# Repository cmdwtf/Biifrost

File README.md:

# Biifröst Bridge
A PCB bridge from Odiin to Screen

### Board Images

# EDA
Biifröst Bridge was designed and created with [KiCad EDA](https://kicad.org/) 5.1.6.

# License
This repository is licensed under Apache-2.0 WITH SHL-2.1. Please see LICENSE.md for more information.

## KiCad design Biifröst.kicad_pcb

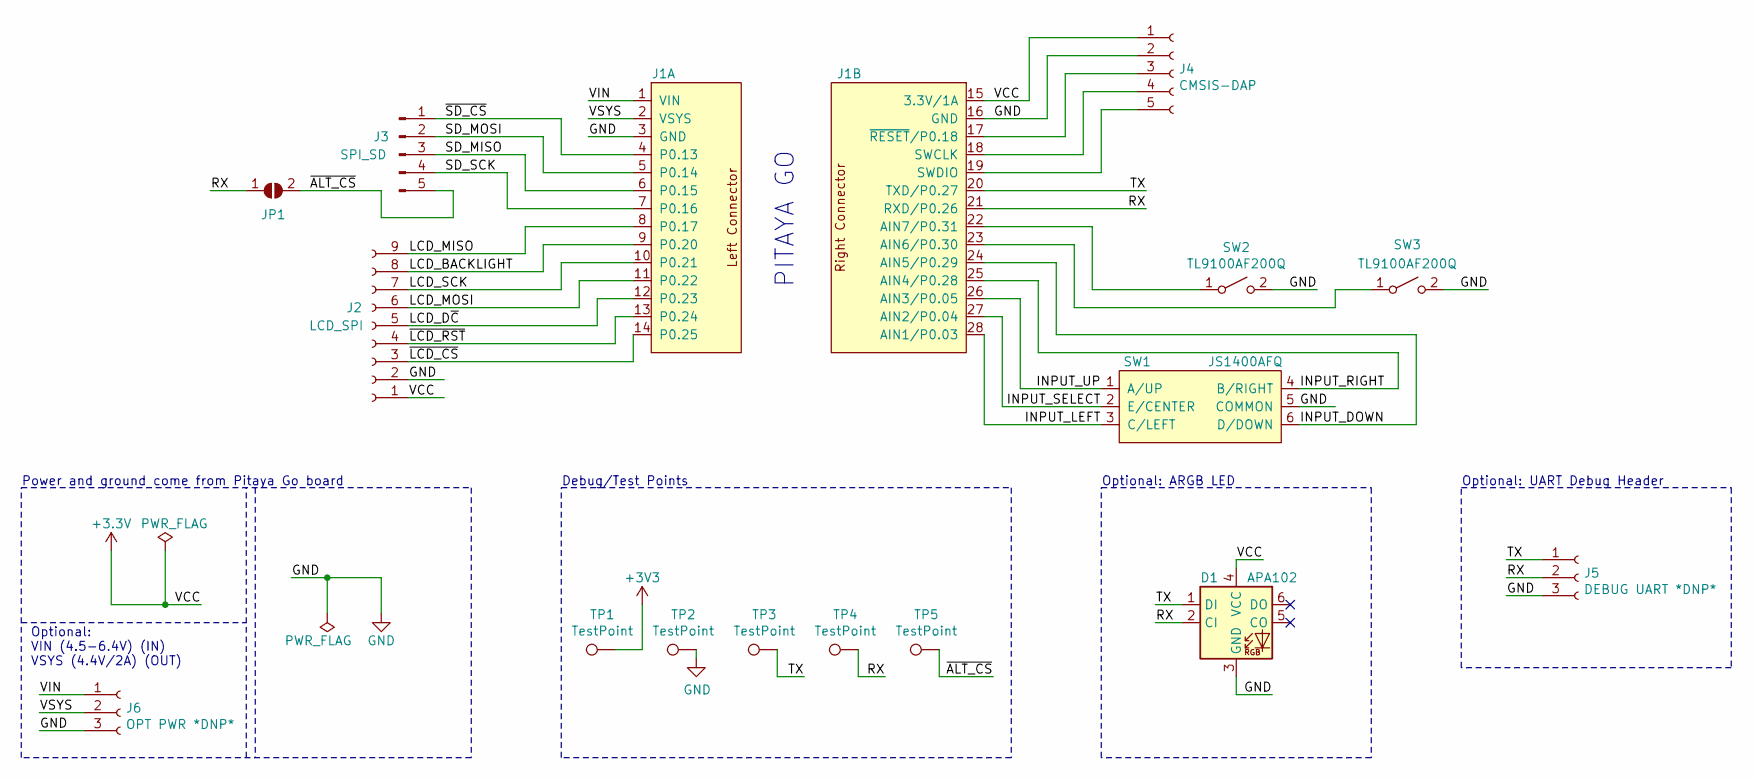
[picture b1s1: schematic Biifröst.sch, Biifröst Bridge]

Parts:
D1: APA102; LED_RGB_5050-6
J1: Pitaya_Go; Pitaya_Go_Headers
J2: LCD_SPI; PinHeader_1x09_P2.54mm_Vertical
J3: SPI_SD; PinHeader_1x05_P2.54mm_Vertical
J4: CMSIS-DAP; PinHeader_1x05_P2.54mm_Horizontal
J5: DEBUG UART *DNP*; PinHeader_1x03_P2.54mm_Horizontal
J6: OPT PWR *DNP*; PinHeader_1x03_P2.54mm_Horizontal
JP1: SolderJumper_2_Open; SolderJumper-2_P1.3mm_Open_TrianglePad1.0x1.5mm
SW1: JS1400AFQ; JS1400
SW2, SW3: TL9100AF200Q; TL9100
TP1, TP2, TP3, TP4, TP5: TestPoint; TestPoint_Pad_D1.5mm

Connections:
/INPUT_DOWN: J1.24 (AIN5/P0.29), SW1.6 (D/DOWN)
/INPUT_LEFT: J1.28 (AIN1/P0.03), SW1.3 (C/LEFT)
/INPUT_RIGHT: J1.25 (AIN4/P0.28), SW1.4 (B/RIGHT)
/INPUT_SELECT: J1.27 (AIN2/P0.04), SW1.2 (E/CENTER)
/INPUT_UP: J1.26 (AIN3/P0.05), SW1.1 (A/UP)
/LCD_BACKLIGHT: J1.9 (P0.20), J2.8
/LCD_D~C~: J1.12 (P0.23), J2.5
/LCD_MISO: J1.8 (P0.17), J2.9
/LCD_MOSI: J1.11 (P0.22), J2.6
/LCD_SCK: J1.10 (P0.21), J2.7
/RX: D1.2 (CI), J1.21 (RXD/P0.26), J5.2, JP1.1 (A), TP4.1
/SD_MISO: J1.6 (P0.15), J3.3
/SD_MOSI: J1.5 (P0.14), J3.2
/SD_SCK: J1.7 (P0.16), J3.4
/TX: D1.1 (DI), J1.20 (TXD/P0.27), J5.1, TP3.1
/VIN: J1.1 (VIN), J6.1
/VSYS: J1.2 (VSYS), J6.2
/~ALT_CS~: J3.5, JP1.2 (B), TP5.1
/~LCD_CS~: J1.14 (P0.25), J2.3
/~LCD_RST~: J1.13 (P0.24), J2.4
/~SD_CS~: J1.4 (P0.13), J3.1
GND: D1.3 (GND), J1.3 (GND), J1.16 (GND), J2.2, J4.2, J5.3, J6.3, SW1.5 (COMMON), SW2.2 (B), SW3.2 (B), TP2.1
unnamed: J1.17 (~RESET~/P0.18), J4.3
unnamed: J1.18 (SWCLK), J4.4
unnamed: J1.19 (SWDIO), J4.5
unnamed: J1.22 (AIN7/P0.31), SW2.1 (A)
unnamed: J1.23 (AIN6/P0.30), SW3.1 (A)

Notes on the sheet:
PITAYA GO
Power and ground come from Pitaya Go board
Optional: ARGB LED
Optional: UART Debug Header
Debug/Test Points
Optional: VIN (4.5-6.4V) (IN) VSYS (4.4V/2A) (OUT)

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
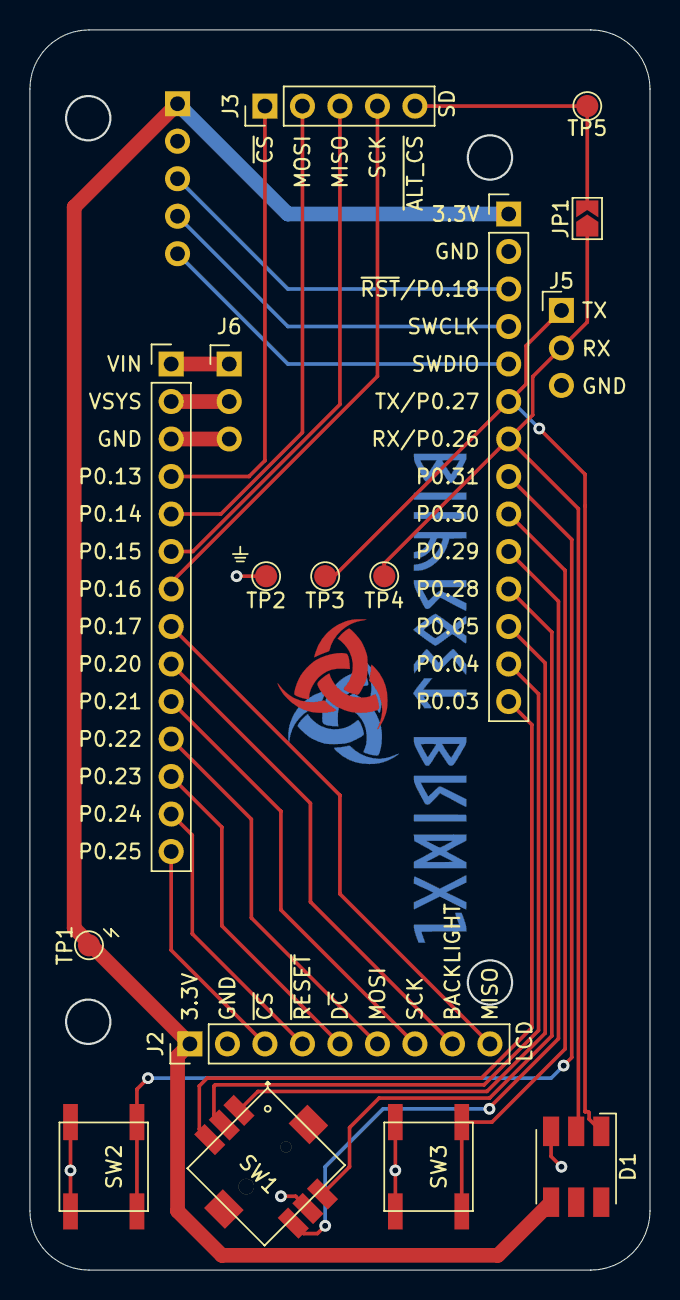
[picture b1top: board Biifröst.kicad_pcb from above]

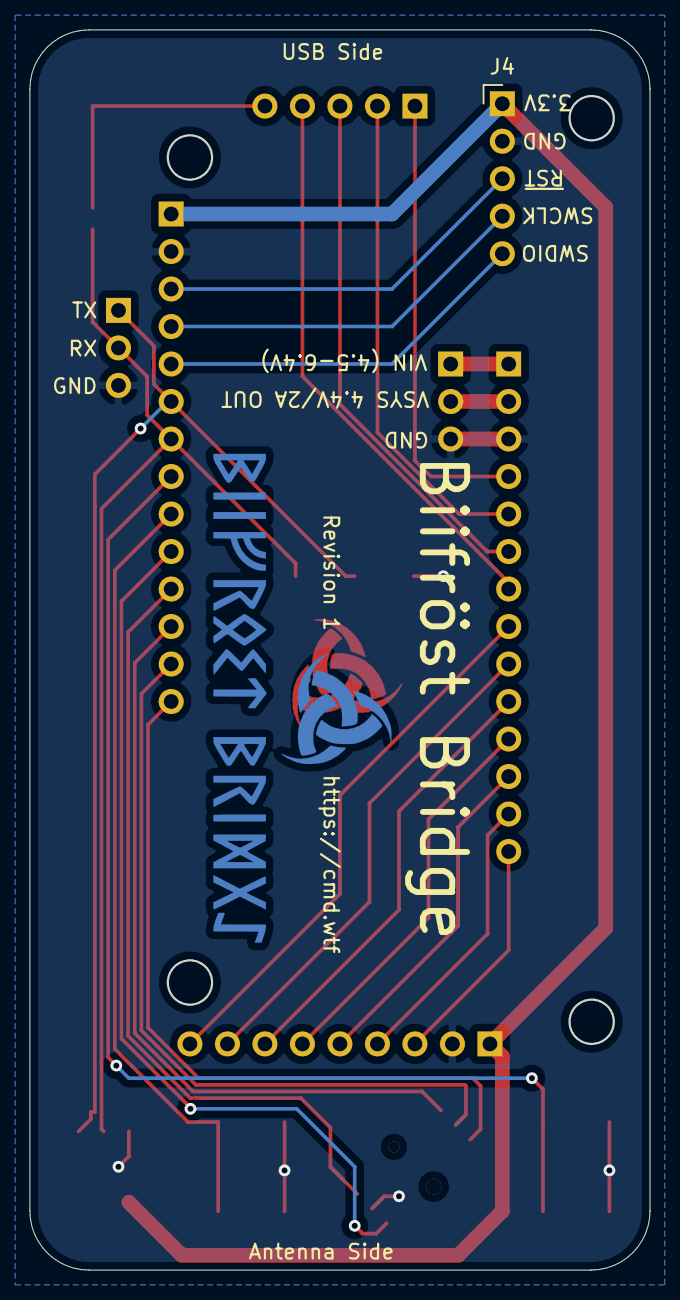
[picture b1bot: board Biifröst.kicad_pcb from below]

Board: 2 copper layers, 41.9 x 83.9 mm, 19 parts (3 on the bottom side), 28 nets.

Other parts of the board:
Ref**: Val**; Horn_of_Odin
Ref**#2: Val**; Logo
Ref**#3: Val**; Wordmark

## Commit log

2020-08-03 WIP r0.
2020-08-03 Add Wordmark/Icon for flair.
2020-08-11 Add Apache-2.0 WITH SHL-2.1 license.
2020-08-11 Add board images for r0.
2020-08-11 Fix README.md markdown.
2020-08-11 Update README.md
    Replaced markdown for images with HTML, so I could scale them to not be so giant :)
2020-08-18 Add several models.
    Including Pitaya Go, both E-Switch types.
    Added some board dimensions too.
2020-08-18 Update pins to have not bars where they should be.
    And fixed a dumb typo on a net name.
2020-08-19 Add actual board images, fab'd by oshpark.
2020-08-19 Add/adjust some silks. Bump to r1.
    Still need to test the apa102 at 3.3v before I send it up for another spin.
2020-08-21 Add VIN/VSYS breakout. Add 4 hole cuts that will line up with sister boards.
    2 hole cuts will align with the pitaya go holes (1 top, 1 bottom, on one side)
    2 hole cuts will align with the LCD board holes (1 top, 1 bottom, opposite side from pitaya.)
    Not perfectly ideal, but required no trace moves, and they may be useful.
2020-08-21 Add measurements to new hole cuts.
2020-09-27 Update GitHub URLs.
2021-11-10 Update README.md
    https://forum.kicad.info/t/warning-avoid-all-links-to-kicad-pcb-org-use-kicad-org/31521
